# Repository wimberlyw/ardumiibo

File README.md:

# Arduboy Pro Rumble - With Ardumiibo Scanner
### The Arduboy Pro Rumble itself is a homemade Leonardo backpack that has a vibration motor attached to Speaker Pin 2. Game makers can use the Arduboy2 Tones commands to add rumble to their game. The system also features broken out Serial connection to connect the the Ardumiibo Scanner and future peripherals.

### The Ardumiibo scanner is a PN532 NFC Scanner with a Neopixel ring that can scan collectible items from the real world into your game. 

## An Arduboy based nod to Tiger Electronics handhelds, Rumble Features, and [Amiibos](https://www.nintendo.com/amiibo/)

### [Watch The Youtube Playlist Before You Begin](https://youtube.com/playlist?list=PLI37KAai0mUhJ3Yi7gZaNxqZhPj6SuK46)

# TOC

1. [Bill of Materials](https://github.com/wimberlyw/ardumiibo#materials-needed)
2. [Assembly](https://github.com/wimberlyw/ardumiibo#assembly)
    - Arduboy Pro Rumble Game Console
    - Powerboost
    - Boost Cables
    - Scanner
3. [Software](https://github.com/wimberlyw/ardumiibo#software)
4. [Examples](https://github.com/wimberlyw/ardumiibo#load-your-scanner-pro-micro-up-with-the-nfc-reader)  

## Materials Needed:

### Arduboy Pro Rumble:
- Arduino Leonardo
- 10mm x 2.5mm Disc Shape Vibration Motor for Cell Phone - 3v
  - Mine was from uxcel but these look just as good. (https://www.amazon.com/tatoko-12000RPM-Wired-Phone-Vibration/dp/B07L5V5GYG/ref=sr_1_2?dchild=1&keywords=vibration+motor+cell+phone&qid=1624498175&sr=8-2)
 - 2n2222 NPN transistor
 - 3x 110 ohm resistors
 - 10uF 50V capacitor
 - Diode
 - 7x tactile momentary push buttons
 - RGB LED
 - piezo buzzer
 - On off switch
 - 2.42" i2c SSD1309 OLED
 - USB data cable (for booster cable)
 - [3d printer files](https://github.com/wimberlyw/ardumiibo/tree/main/3d%20parts)
 - [Adafruit Powerboost 500](https://www.adafruit.com/product/1944)
    - [Booster cable for Powerboost](https://learn.adafruit.com/booster-cable)
- [3.7V 1200mAh Lipo Battery](https://www.amazon.com/gp/product/B00J2QET64/ref=ppx_yo_dt_b_search_asin_title?ie=UTF8&psc=1)

### Ardumiibo Scanner
-  [3d printer files](https://github.com/wimberlyw/ardumiibo/tree/main/3d%20parts)
-  [24LED Neopixel ring] (https://www.amazon.com/gp/product/B0774JNSCF/ref=ppx_yo_dt_b_search_asin_title?ie=UTF8&psc=1)
-  [PN532 NFC Reader](https://www.amazon.com/gp/product/B01I1J17LC/ref=ppx_yo_dt_b_search_asin_title?ie=UTF8&psc=1)
- USB data cable (for booster cable)
- [Adafruit Powerboost 500](https://www.adafruit.com/product/1944)
- On off switch
- [Booster cable for Powerboost](https://learn.adafruit.com/booster-cable)
- [3.7v 500 mAh Lipo battery](https://www.amazon.com/gp/product/B00L0W61VO/ref=ppx_yo_dt_b_search_asin_title?ie=UTF8&psc=1)
- Leonardo Pro Micro
- Perfboard to mount up everything nice 
- NFC stickers for ardumiibos. (https://www.amazon.com/THONSEN-NTAG215-Stickers-Perfectly-NFC-Enabled/dp/B07MKWHYQK/ref=sr_1_5?dchild=1&keywords=rfid+stickers&qid=1624482994&sr=8-5)
- 

## Assembly
  	- Good luck.
  - Add hot glue as wire stress relief as you go. 
  
- Start printing the 3d printer files listed in the 3d parts section of this Github or listed in the BOM above. 

### Arduboy Pro Rumble
- You can either contact me for a pcb and I can order some more, you can make your own using the schematics from the giuthub, or you can breadboard this out. Up to you. 

### Front side PCB
1. Solder the Male header pins into the middle of the PCB so that it's like a backpack for the Leonardo. The Male pins on the PCB face **DOWN** towards the Leonardo female pins. 

2. Solder in your two resistors top right, and the 7x tactile buttons onto the top of the board. 
3. Solder in your Screen. All the pins should line up on the left hand side. If you're breadboarding this, refer to the schematics for how to hook up the display.
  -  The only items facing the front of the PCB are the buttons and those two resistors. And the Screen

### Back Side PCB

1. Install female header pins where the broken out ICSP header is. 
2. Directly beneath the female header pins, install the third resistor. 
3. Solder in the transistor with the flat part facing up, curved part towards the bottom. 
4. Solder in the diode with the white stripe facing the way it is on the board. Once again refer to the schematic for help, or the pictures on the pcb. 
5. Install the capacitor with negative stripe facing the right. 

- I would install the Speaker, vibraating motor, and RGBLED on the back of the PCB. 

6. The vibrating motor goes on the two holes to the right of the capacitor circuit. Install the vibrating motor with ground wire on the left. (If PCB back is facing you.)

7. The speaker is labeled for the front, but I find it works better on the bottom of the board. the speaker wire holes are directly left of the diode.(If PCB back is facing you.) Solder in the piezo speaker with the positive wire on the left.

8. The serial cable wires are also labeled for the top, but I like them better on the bottom. You should be able to see the traces on the PCB. If the back of the OCB is facing you RX is the left hole of the gold pads. TX is the right. (the front of the board has them labeled as JP1.)

9. You're also going to need to tack a ground wire onto one of the nubs of a ground wire, as you need this for serial and I forgot. 
- This illustrates the ground wire, but the other wires are on top, which I mentioned not to do. 

##
## At this point you should be able to backpack the PCB onto the Leonardo
##
### Now we need to make the booster cables so we can power up the arduino.
  - You should probably hook everything up to your data cable at this point and run the included "Rumble Demo" to make sure everything's working right. We're about to cut up that data cable so, test it now, anyway. 
  -
  
 ## Powerboost and Booster Cables
 
 1. Follow the directions from Adafruit to hook up a switch to your Powerboost. You're going to want to mount the switch with wires instead of directly to the board so we can remote mount it. 
  - https://learn.adafruit.com/adafruit-powerboost-500-plus-charger/on-slash-off-switch

  - 

### You may as well wire up both powerboosts, and make two boost cables. We need the boost cables to be able to pass data through . 

2. https://learn.adafruit.com/booster-cable

## It's Time To
## Shove thaat thang in the case.
### Let me just preface this with I didn't know the powerboost would take up so much room. They look so small. 
### And I'm new to Fusion360. 
#### Sowwy. 
#### Do your best to put everything in the case and rout the USB out the top holes, and the Serial cable out the bottom. It's pretty self explanatory so here are some pictures of how I did it. Feel free to design your own case at this point. 

#### Glue down the Piezo and the vibrating motor to the back inside of the, where the empty resources are. You probably want to add a few dabs of glue to the front part of the case to keep your d pad in place, too. 

## Should look like this 

## Ardumiibo Scanner Assembly

1. On the **PN532 NFC RFID module** Solder on the 4 90 degree pins that came with your module so that they are sticking out the side that reads "TXD RXD"
2. Carefully switch the module to IIC/ I2c mode by flipping the jumper. 
  - More info can be found here: https://www.electroschematics.com/nfc-rfid-module-pn532/
  - And here: http://wiki.sunfounder.cc/index.php?title=PN532_NFC_RFID_Module
3. The Arduino Pro Micro will sit in the bottom of the Scanner case, along with the Powerboost hooked up to it's booster cable
 - https://learn.adafruit.com/booster-cable
4. The middle bdoy is where the PN532 will sit, and you will pass wires through the holes to the bottom of the case.  (If you've printed the case this will be very evident.)
5. The top faceplate is in 3 parts, and the NEOPIXEL ring is glued into the back of the light diffuser ring part. 
6. Run the wires from the top section of the box where the LEDs are, THrough the body, and into the base so you can solder them into the Pro Micro as follows. 

Pro Micro | Module
------------ | -------------
VCC | VCC PN532
VCC | 5v LED Ring 
GND | GND PN532
GND | GND LED Ring
Pin 2 | PN532/ SDA
PIN 3 | PN532/ SCL
PIN 4 | LED Ring Data In

### Unfortunately I can't show you the wires in the pro micro because fitting everything in the box is a hard task. Once it's in there, it's in. 
 - Use plenty of hot glue for attaching and wire stress relief. 

## Software

- I use the Arduino IDE so I can't speak to the Arduboy game loaders. 
- Use Mr Blinky's homemade Package for running the 1309. Select Homemade Arduboy, Leonardo, and SSD1309. Standard Arduino Core.
  - https://github.com/MrBlinky/Arduboy-homemade-package
  - Blinky's software worked for me out of the box, but I remember way back having to change some addresses or running the patcher for uploading games. You can find out all about that on the Arduboy forums and in Mr. Blinky's docs. 

- Install the PN532 Arduino Library
  - https://github.com/Seeed-Studio/PN532/tree/arduino/PN532

- Install the Adafruit Neopixel Library 
  - https://learn.adafruit.com/adafruit-neopixel-uberguide/arduino-library-installation

### Load your scanner Pro Micro up with the NFC Reader 

- (https://github.com/wimberlyw/ardumiibo/tree/main/Scanner%20Programs)
    -  This is basically boilperplate from the PN532 libraries, and the Adafruit Neopixel library.

### Load your Arduboy Pro Rumble up with the example ScanDemo

-https://github.com/wimberlyw/ardumiibo/tree/main/Examples
 
 ### Check out the video tutorial on how to make an Ardumiibo. 
 
 - https://youtu.be/rNLjulla09I
  - Use the word "keys" for the key example
  - Use "pots" for the potion example. 
  - Try Everything out!
 
 ## Try the "Turbo Waddle" Demo!
 
 - https://youtu.be/9yPsy_AzS58
 - https://github.com/wimberlyw/ardumiibo/tree/main/Game/TurboWaddle

## Make your own game with Rumble!

- Rumble just uses the Tone library BeepPin2. 
- Essentially The scanner is just passign a string over serial. 
  -  Read the examples!

```BeepPin2 rumble; // Rumble motor runs on Speaker Pin 2

void setup() 
{rumble.begin();//Set up Rumble Motor}
  
	 if (arduboy.justPressed(B_BUTTON)) {

	rumble.tone(beep.freq(523.251), 5); /beep.freq(523.251) is used to convert 523.251Hz to the required count
	} 
```
 
## Make your own game with Ardumiibo Support!
1. Turn on :
  - ` power_usart1_enable(); // Arduboy turns off serial power, so we need that to connect to the RFID reader`
  -  `Serial1.begin(115200);// Begin communication with the Serial port/ Reader over Serial 1"` 

 2. Set up a dummy string to save the message we receive from Serial. 
`String Message;//Storing messages from the scanner as a string here. `

3. If the Serial is receiving a message, check to see if it's ours.
- If it is, do something. 

**THIS LINE MAKES SERIAL NOT LOCK UP EVERYTHING BY SCANNING ALL THE TIME, BUT ONLY WHEN DATA COMES
You could do a "Blocking" version if you wanted the user to be stuck somewhere until they scan something.  Just don't include serial available.**

`if(Serial1.available()){  
   Message = Serial1.readStringUntil('\r');     //Store incoming data `

      if(Message != ""){    
        
        //We've found that the writer apps put an extra " en/" in the string, so we take it out. 
        Message.remove(0,3);

        // if it exists, do stuff.
          if(Message.indexOf(potionCode) >= 0){      //if our code exists in what was scanned
                                    //do stuff
            Serial1.flush();   //Clear the serial buffer of any info
            arduboy.delayShort(1000);    //add a lil delay time
            heartsEarned++; 
           }

### **That's really all you need to set up your game to read from the scanner!**

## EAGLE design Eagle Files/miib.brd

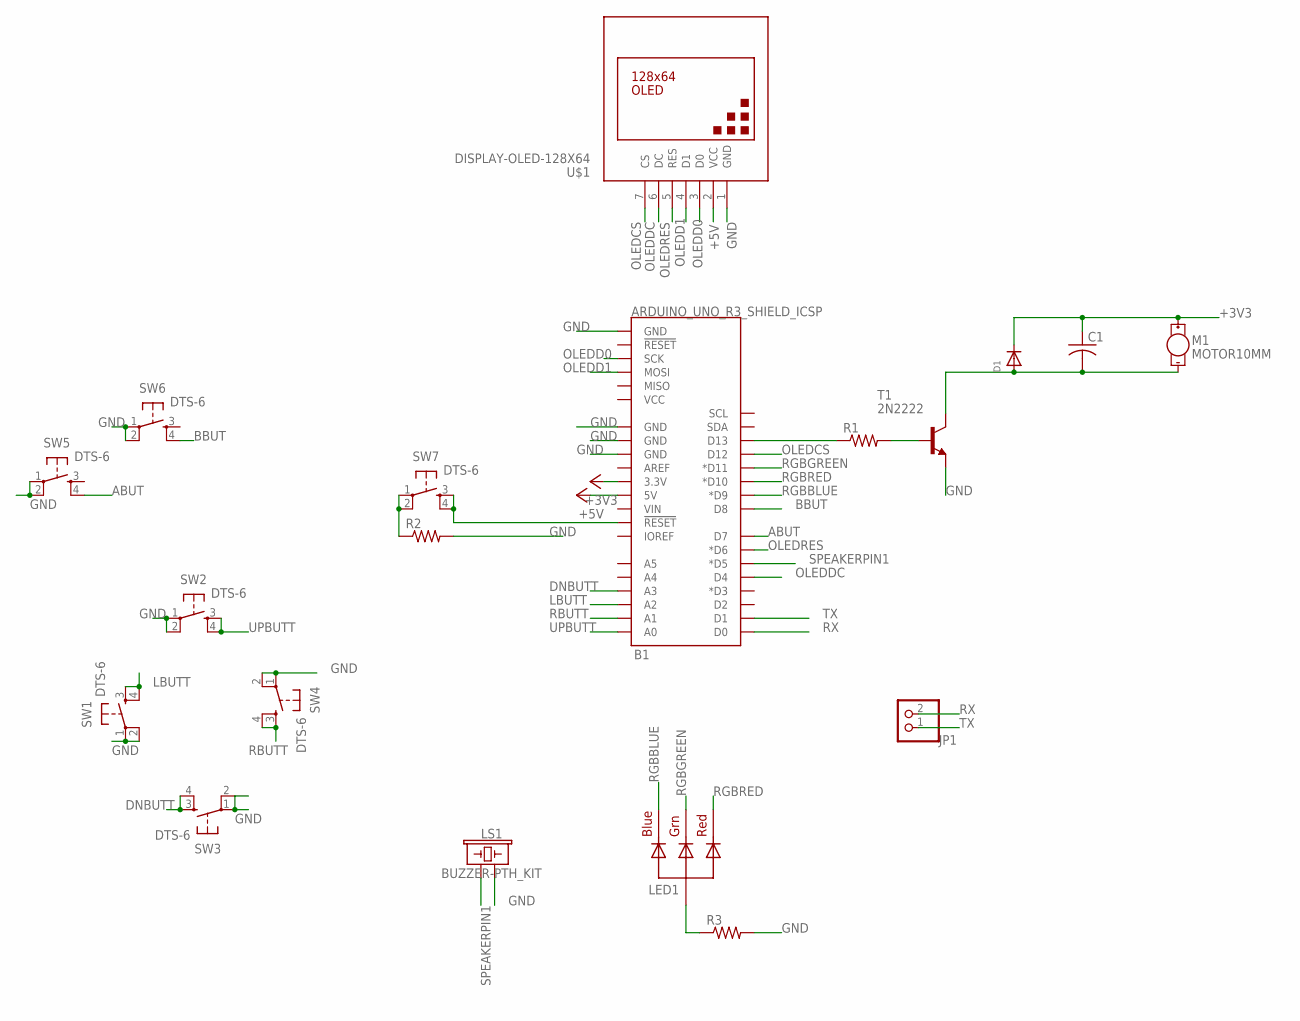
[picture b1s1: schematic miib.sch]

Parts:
B1: ARDUINO_UNO_R3_SHIELD_ICSP; UNO_R3_SHIELD_ICSP
C1: C-US025-025X050; C025-025X050
D1: DIODEDO-1N4148; DO-1N4148
JP1: PINHD-1X2/90; 1X02/90
LED1: RGBLED_CA-5MM; LED5MMRGB
LS1: BUZZER-PTH_KIT; BUZZER-12MM-KIT
M1: MOTOR10MM; VIBE-MOTOR-10MM
R1, R2, R3: R-US_0204/7; 0204/7
SW1, SW2, SW3, SW4, SW5, SW6, SW7: DTS-6
T1: 2N2222; TO92-EBC-OVAL
U$1: DISPLAY-OLED-128X64

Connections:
+3V3: B1.3.3V, C1.1, D1.C, M1.+
+5V: B1.5V, U$1.2 (VCC)
ABUT: B1.D7, SW5.4
BBUT: B1.D8, SW6.4
DNBUTT: B1.A3, SW3.3, SW3.4
GND: B1.GND@0 (GND), B1.GND@1 (GND), B1.GND@2 (GND), B1.GND_ICSP (GND), LS1.- (2), R2.2, R3.2, SW1.1, SW1.2, SW2.1, SW2.2, SW3.1, SW3.2, SW4.1, SW4.2, SW5.1, SW5.2, SW6.1, SW6.2, T1.E, U$1.1 (GND)
LBUTT: B1.A2, SW1.3, SW1.4
unnamed: B1.D13, R1.1
unnamed: R1.2, T1.B
unnamed: R2.1, SW7.1, SW7.2
unnamed: B1.RES (!RESET!), SW7.3, SW7.4
unnamed: C1.2, D1.A, M1.-, T1.C
unnamed: LED1.2 (VCC), R3.1
OLEDCS: B1.D12, U$1.7 (CS)
OLEDD0: B1.SCK, U$1.3 (D0)
OLEDD1: B1.MOSI, U$1.4 (D1)
OLEDDC: B1.D4, U$1.6 (DC)
OLEDRES: B1.D6 (*D6), U$1.5 (RES)
RBUTT: B1.A1, SW4.3, SW4.4
RGBBLUE: B1.D9 (*D9), LED1.4 (BLUE)
RGBGREEN: B1.D11 (*D11), LED1.3 (GREEN)
RGBRED: B1.D10 (*D10), LED1.1 (RED)
RX: B1.RX (D0), JP1.2
SPEAKERPIN1: B1.D5 (*D5), LS1.+ (1)
TX: B1.TX (D1), JP1.1
UPBUTT: B1.A0, SW2.3, SW2.4

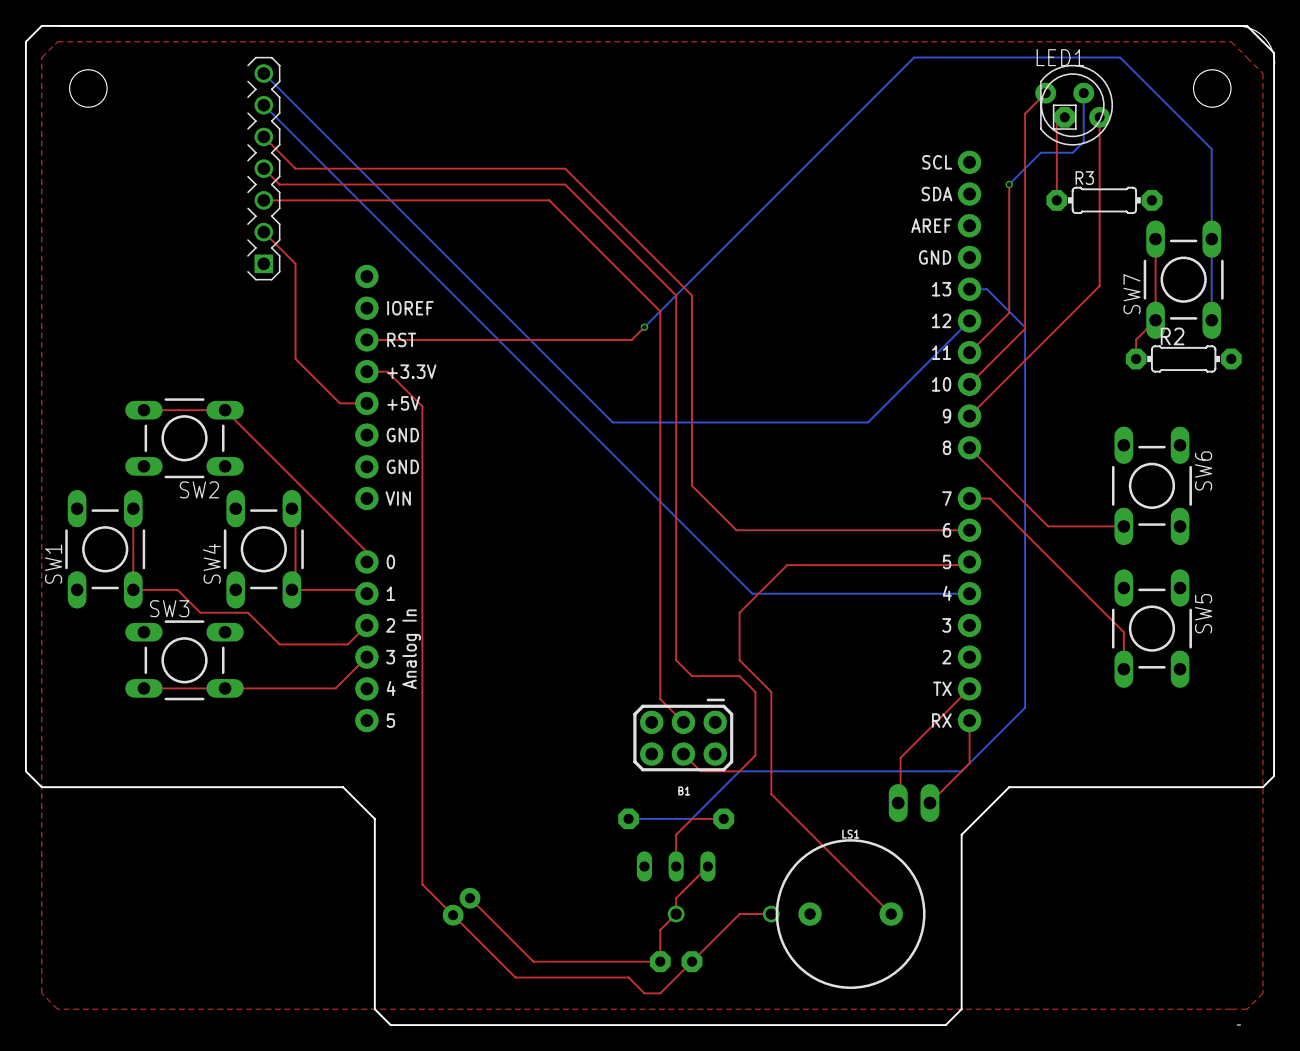
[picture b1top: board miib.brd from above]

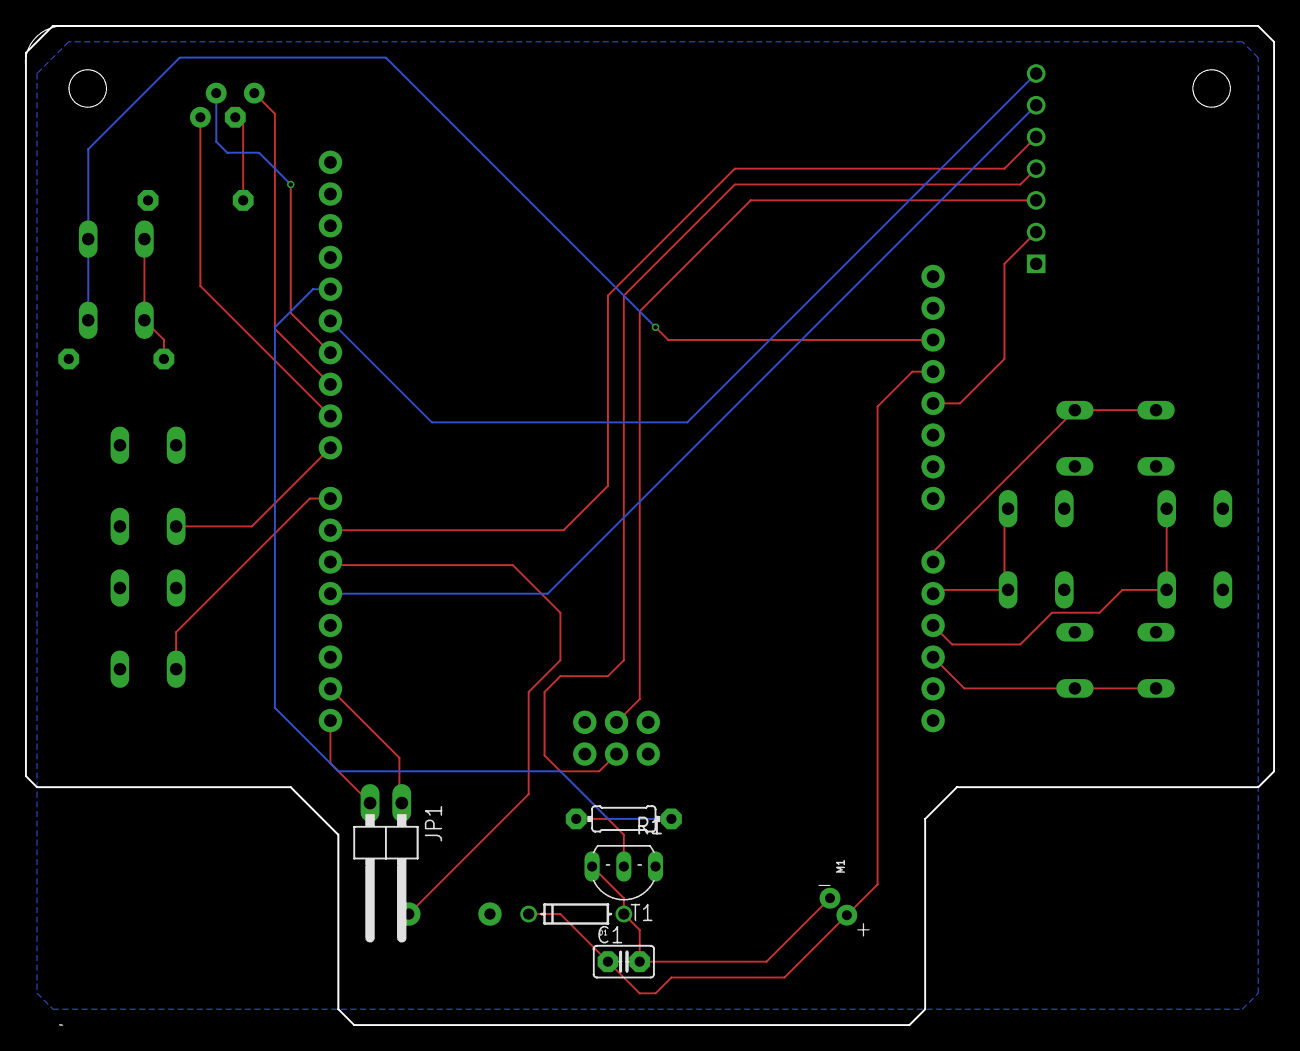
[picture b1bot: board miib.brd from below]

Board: 2 copper layers, 99.9 x 80.0 mm, 19 parts (6 on the bottom side), 26 nets.

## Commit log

2021-06-21 do
    yes
2021-06-21 Turbo Waddle Game
    Add
2021-06-21 Less Gameception
    Added
2021-06-21 Rumble Demo
    Rumble Example
2021-06-24 Large Update
    3d parts, examples, and game
2021-06-24 Remove duplicate files
2021-06-24 images folder added
2021-06-24 Updated BOM
2021-06-24 updated install pics
2021-06-24 groundwirepic
2021-06-24 onOff
2021-06-24 Final Readme Pics
    Pic Dump
2021-06-24 Eagle Files Added
2021-06-24 updated cover photo
2021-06-25 updated doc

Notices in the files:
parts and their libraries:
SparkFun-Electromechanical: Licensing: Creative Commons ShareAlike 4.0 International - https://creativecommons.org/licenses/by-sa/4.0
